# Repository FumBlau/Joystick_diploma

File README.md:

# Joystick_diploma
Diploma entregado a los asistentes al curso de Kicad y soldadura SMD del colegio Juan Comenius

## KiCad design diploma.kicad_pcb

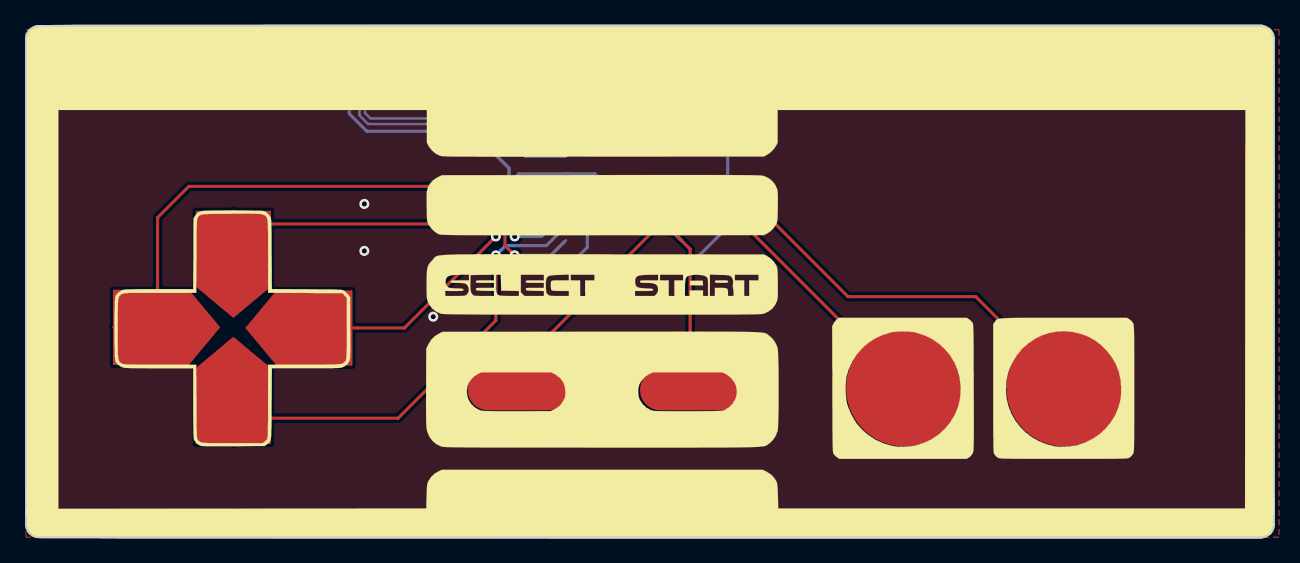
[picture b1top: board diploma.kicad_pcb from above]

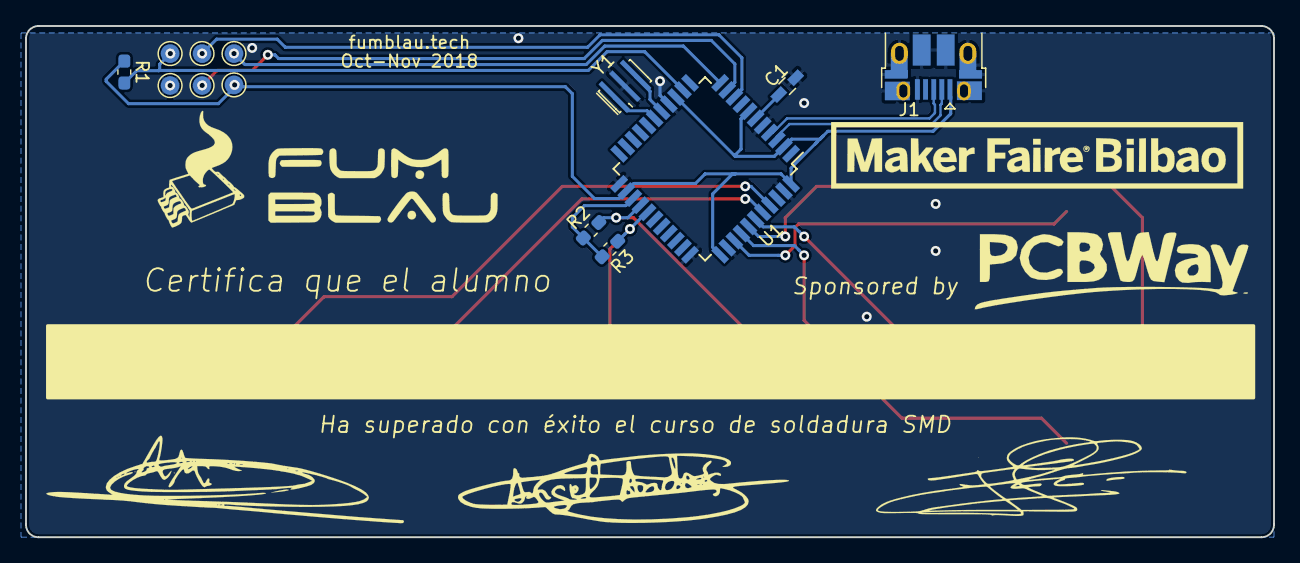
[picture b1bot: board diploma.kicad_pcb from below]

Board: 2 copper layers, 99.6 x 40.8 mm, 21 parts (13 on the bottom side), 20 nets.

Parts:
BT1, BT2, BT3, BT4: Pad_arrow; Pad_arrow_2_muy_corto
BT5, BT7: pad_btn; pad_btn_2
BT6, BT8: pad_btn; pad_btn_3
C1: 1uF; C_0603_HandSoldering
J1: USB_B_Micro; USB_Micro-B_Amphenol_10103594-0001LF_Horizontal
R1: R; R_0603_1608Metric_Pad1.05x0.95mm_HandSolder
R2, R3: 1M; R_0603_1608Metric_Pad1.05x0.95mm_HandSolder
TP1, TP2, TP3, TP4, TP5, TP6: TestPoint; TestPoint_Pad_D1.5mm
U1: ATmega32U4-AU; TQFP-44_10x10mm_P0.8mm
Y1: Crystal_GND2; Resonator_SMD_muRata_CSTxExxV-3Pin_3.0x1.1mm_HandSoldering

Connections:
+5V: J1.1, R1.1, TP4.1, U1.2, U1.7, U1.14, U1.24, U1.34, U1.44
/CLK: TP2.1, U1.9
/MISO: TP3.1, U1.11
/MOSI: TP5.1, U1.10
/USB_N: J1.2, U1.3
/USB_P: J1.3, U1.4
/btn1: BT5.1, U1.41
/btn2: BT7.1, U1.40
/btn3: BT6.1, R2.2, U1.26
/btn4: BT8.1, R3.2, U1.27
/down: BT3.1, U1.37
/ida: R2.1, R3.1, U1.25
/left: BT1.1, U1.38
/reset: R1.2, TP1.1, U1.13
/right: BT4.1, U1.39
/up: BT2.1, U1.36
GND: C1.2, J1.5, J1.6, TP6.1, U1.5, U1.15, U1.23, U1.33, U1.35, U1.43, Y1.2
unnamed: C1.1, U1.6
unnamed: U1.16, Y1.3
unnamed: U1.17, Y1.1

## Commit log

2019-10-10 - Modificado para Maker Faire Bilbao
2019-10-22 - Cambio header de programacion por pads con via en el medio - Añado logo PCBWay para que nos patrocinen Bilbao
